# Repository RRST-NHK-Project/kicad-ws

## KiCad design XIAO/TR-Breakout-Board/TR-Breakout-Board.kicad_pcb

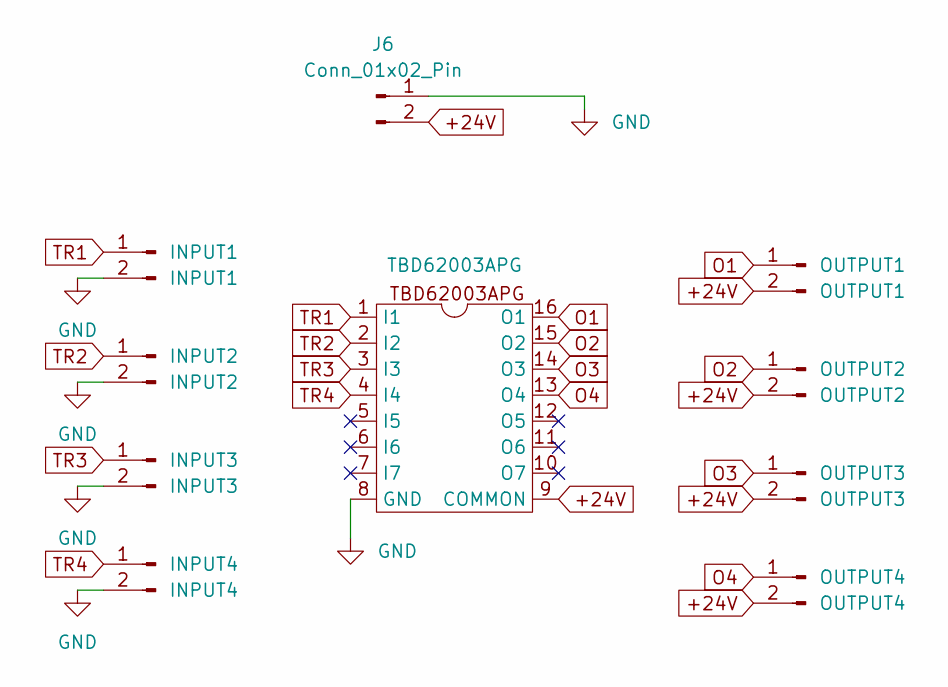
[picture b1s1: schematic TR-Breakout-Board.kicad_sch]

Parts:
INPUT1: INPUT1; JST_XH_B2B-XH-A_1x02_P2.50mm_Vertical
INPUT2: INPUT2; JST_XH_B2B-XH-A_1x02_P2.50mm_Vertical
INPUT3: INPUT3; JST_XH_B2B-XH-A_1x02_P2.50mm_Vertical
INPUT4: INPUT4; JST_XH_B2B-XH-A_1x02_P2.50mm_Vertical
J6: Conn_01x02_Pin; AMASS_XT30U-M_1x02_P5.0mm_Vertical
OUTPUT1: OUTPUT1; JST_XH_B2B-XH-A_1x02_P2.50mm_Vertical
OUTPUT2: OUTPUT2; JST_XH_B2B-XH-A_1x02_P2.50mm_Vertical
OUTPUT3: OUTPUT3; JST_XH_B2B-XH-A_1x02_P2.50mm_Vertical
OUTPUT4: OUTPUT4; JST_XH_B2B-XH-A_1x02_P2.50mm_Vertical
TBD62003APG: DIP-16_W7.62mm

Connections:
+24V: J6.2, OUTPUT1.2, OUTPUT2.2, OUTPUT3.2, OUTPUT4.2, TBD62003APG.9 (COMMON); also elsewhere on the board
GND: INPUT1.2, INPUT2.2, INPUT3.2, INPUT4.2, J6.1, TBD62003APG.8 (GND); also elsewhere on the board
O1: OUTPUT1.1, TBD62003APG.16 (O1); also elsewhere on the board
O2: OUTPUT2.1, TBD62003APG.15 (O2); also elsewhere on the board
O3: OUTPUT3.1, TBD62003APG.14 (O3); also elsewhere on the board
O4: OUTPUT4.1, TBD62003APG.13 (O4); also elsewhere on the board
TR1: INPUT1.1, TBD62003APG.1 (I1); also elsewhere on the board
TR2: INPUT2.1, TBD62003APG.2 (I2); also elsewhere on the board
TR3: INPUT3.1, TBD62003APG.3 (I3); also elsewhere on the board
TR4: INPUT4.1, TBD62003APG.4 (I4); also elsewhere on the board

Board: 2 copper layers, 10 parts (0 on the bottom side), 10 nets, no tracks yet.

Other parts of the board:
TBD62003APG1: DIP-16_W7.62mm

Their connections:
+24V: TBD62003APG1.9 (COMMON); also elsewhere on the board
GND: TBD62003APG1.8 (GND); also elsewhere on the board
O1: TBD62003APG1.16 (O1); also elsewhere on the board
O2: TBD62003APG1.15 (O2); also elsewhere on the board
O3: TBD62003APG1.14 (O3); also elsewhere on the board
O4: TBD62003APG1.13 (O4); also elsewhere on the board
TR1: TBD62003APG1.1 (I1); also elsewhere on the board
TR2: TBD62003APG1.2 (I2); also elsewhere on the board
TR3: TBD62003APG1.3 (I3); also elsewhere on the board
TR4: TBD62003APG1.4 (I4); also elsewhere on the board

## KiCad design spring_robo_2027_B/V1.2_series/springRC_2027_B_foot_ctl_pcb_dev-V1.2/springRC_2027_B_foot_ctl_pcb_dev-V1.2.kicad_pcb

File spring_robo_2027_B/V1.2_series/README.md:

# V1.2 系 設計案

V1.1（EOD）で配線が成立しなかったため、部品構成を変えた6案をプロジェクトとして複製したもの。
回路の中身以外（基板外形・層構成・ネットクラス・部品ライブラリ）は全案共通。

## 命名規則

| 位置 | 記号 | 意味 |
|---|---|---|
| 接頭 | なし | エンコーダのバッファを廃止 |
| 接頭 | `b` | バッファを 0Ω抵抗からソルダージャンパ（既定開放）に変更 |
| 接頭 | `fb` | バッファを強制有効（選択用の 0Ω抵抗を廃止） |
| 接尾 | `cmp` | QI 拡張ヘッダ J8 / J9 あり |
| 接尾 | なし | QI 拡張ヘッダ J8 / J9 なし |
| 例外 | `org` | V1.1 のまま（バッファ + 0Ω選択式 + QI） |

## 一覧

| 案 | バッファ | QI | 部品 | ネット | ERC | エラー |
|---|---|---|---|---|---|---|
| `V1.2org`  | 0Ω選択式 | あり | 71 | 63 | 29 | 0 |
| `V1.2bcmp` | ジャンパ式 | あり | 71 | 63 | 29 | 0 |
| `V1.2b`    | ジャンパ式 | なし | 74 | 63 | 29 | 0 |
| `V1.2fb`   | 強制有効 | なし | 62 | 63 | 29 | 0 |
| `V1.2cmp`  | なし | あり | 51 | 51 | 29 | 0 |
| `V1.2`     | なし | なし | 54 | 51 | 29 | 0 |

ERC の29件は全て警告。意図的なネットエイリアス28件と、J1 のキャッシュシンボル差異1件。

バッファなし案（`V1.2cmp` / `V1.2`）は `ENC*_BUF` ネットを `ENC*` に統合したためネット数が 51 に減る。
QI なし案は J8 / J9 の削除で単ピンになったネットに TP8〜TP12 を追加している。

## 開発ライン

**`V1.2`**（バッファなし・QIなし）で配線を進める。

## 共通仕様

- U6 = ESP32-S3-WROOM-1-**N16R8**
  - Octal SPI PSRAM が IO35 / IO36 / IO37 を占有するため、この3本は使用不可
  - QIあり案では J9 の 11 / 12 / 13 番ピンが死にピン
  - QIなし案では TP9 / TP10 / TP11 が死にピン
  - 周囲温度 -40〜65℃（PSRAM ECC 有効時は 85℃、容量 1/16 減）
- CAN 終端は R20（120Ω）+ J16（ジャンパ）の直列で CAN_H - CAN_L 間
- 各プロジェクトは `lib/` と `fp-lib-table` / `sym-lib-table` を自前で持つ自己完結構成

## 既知の課題

- 全案とも基板が回路図と未同期。Pcbnew の「回路図から基板を更新」が必要
- 基板は V1.1 の配線（475セグメント / 89ビア）をそのまま継承しているため配線はやり直し
- J1 に `lib_symbol_mismatch` 警告が残る

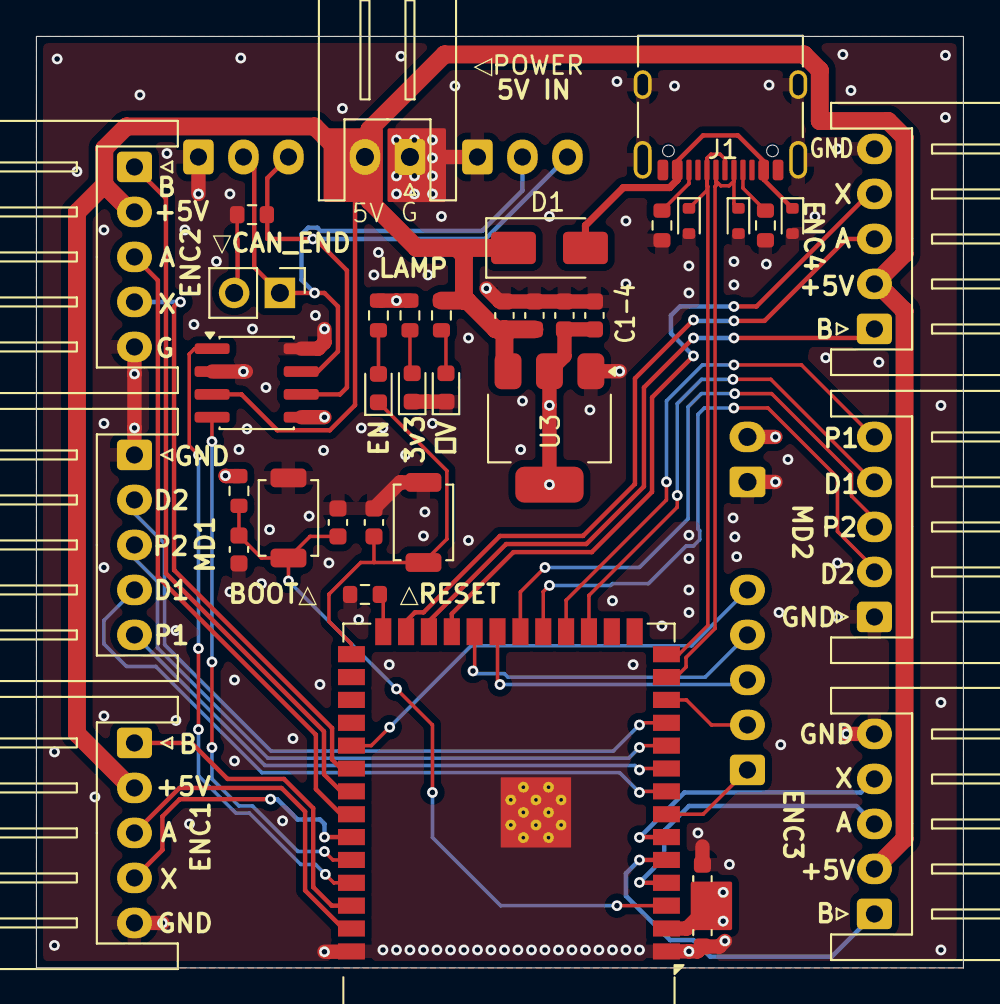
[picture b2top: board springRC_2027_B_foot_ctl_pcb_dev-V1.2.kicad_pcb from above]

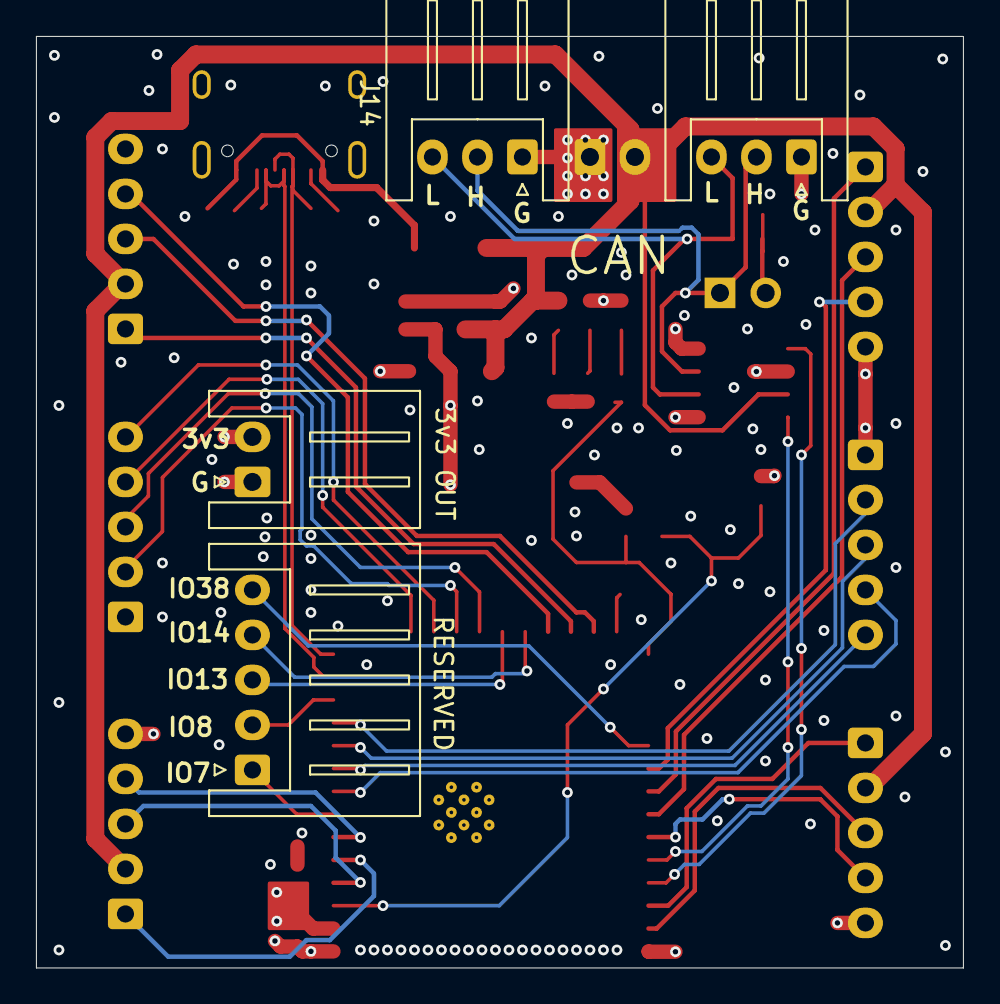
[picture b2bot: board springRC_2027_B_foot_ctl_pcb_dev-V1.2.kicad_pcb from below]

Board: 4 copper layers, 51.5 x 51.8 mm, 42 parts (4 on the bottom side), 44 nets.

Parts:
3v3 OUT: Conn_01x05_Socket; JST_XH_S5B-XH-A_1x05_P2.50mm_Horizontal
C1, C3, C7: 10uF; C_0603_1608Metric
C2, C4, C5, C6, C8: 100nF; C_0603_1608Metric
C9: 1uF; C_0603_1608Metric
D1: SS14; D_SMA
D2, D3, D4: LESD5D5.0CT1G; D_SOD-523
D5, D6, D7: LED; LED_0603_1608Metric
J1: USB_C_Receptacle_USB2.0_16P; USB_C_Receptacle_XKB_U262-16XN-4BVC11
J2, J3, J4, J5, J6, J7: Conn_01x05_Socket; JST_XH_S5B-XH-A_1x05_P2.50mm_Horizontal
J14, J15: Conn_01x03_Socket; JST_XH_S3B-XH-A_1x03_P2.50mm_Horizontal
J16: Conn_01x02_Pin; PinHeader_1x02_P2.54mm_Vertical
R1, R2, R3, R4: 5.1k; R_0603_1608Metric
R5: 10k; R_0603_1608Metric
R6: 330; R_0603_1608Metric
R19: 1k; R_0603_1608Metric
R20: 120; R_0603_1608Metric
RESERVED: Conn_01x02_Socket; JST_XH_S2B-XH-A_1x02_P2.50mm_Horizontal
SW1, SW2: SW_Push; SW_SPST_TS-1088-xR020
U1: MCP2562FD-E-SN; SOIC-8_3.9x4.9mm_P1.27mm
U3: LD1117S33TR_SOT223; SOT-223-3_TabPin2
U6: ESP32-S3-WROOM-1-N16R8; ESP32-S3-WROOM-1
◁POWER : Conn_01x02_Socket; JST_XH_S2B-XH-A_1x02_P2.50mm_Horizontal

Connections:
3V3: C3.2, C4.2, C7.1, C8.1, R2.1, R5.1, R6.2, RESERVED.2, U1.5 (Vio), U3.2 (VO), U6.2 (3V3)
+5V: C1.1, C2.1, D1.1 (K), J2.2, J3.2, J4.2, J5.2, R1.1, U1.3 (VDD), U3.3 (VI), ◁POWER.2
CAN_H: J14.2, J15.2, J16.1, U1.7 (CANH)
CAN_L: J14.3, J15.3, R20.1, U1.6 (CANL)
CAN_RX: U1.4 (RXD), U6.36 (RXD0)
CAN_TX: U1.1 (TXD), U6.37 (TXD0)
DN: D3.1, J1.A7 (D-), J1.B7 (D-), U6.13 (USB_D-)
DP: D4.1, J1.A6 (D+), J1.B6 (D+), U6.14 (USB_D+)
EN: C5.1, C9.1, R5.2, SW1.2, U6.3 (EN)
ENC1_A: J2.3, U6.39 (IO1)
ENC1_B: J2.1, U6.38 (IO2)
ENC1_X: J2.4, U6.35 (IO42)
ENC2_A: J3.3, U6.34 (IO41)
ENC2_B: J3.1, U6.33 (IO40)
ENC2_X: J3.4, U6.32 (IO39)
ENC3_A: J4.3, U6.25 (IO48)
ENC3_B: J4.1, U6.24 (IO47)
ENC3_X: J4.4, U6.23 (IO21)
ENC4_A: J5.3, U6.4 (IO4)
ENC4_B: J5.1, U6.5 (IO5)
ENC4_X: J5.4, U6.6 (IO6)
GND: C1.2, C2.2, C3.1, C4.1, C5.2, C6.2, C7.2, C8.2, C9.2, D2.2, D3.2, D4.2, D5.1 (K), D6.1 (K), J1.A1 (GND), J1.A12 (GND), J1.B1 (GND), J1.B12 (GND), J1.S1 (SHIELD), J2.5, J3.5, J4.5, J5.5, J6.1, J7.1, J14.1, J15.1, R3.2, R4.2, R19.2, RESERVED.1, SW1.1, SW2.1, U1.2 (VSS), U1.8 (STBY), U3.1 (GND), U6.1 (GND), U6.40 (GND), U6.41 (GND), ◁POWER.1
IO0: C6.1, D7.1 (K), SW2.2, U6.27 (IO0)
IO7: 3v3 OUT.1, U6.7 (IO7)
IO8: 3v3 OUT.2, U6.12 (IO8)
IO9: J7.4, U6.17 (IO9)
IO10: J7.5, U6.18 (IO10)
IO11: J7.2, U6.19 (IO11)
IO12: J7.3, U6.20 (IO12)
IO13: 3v3 OUT.3, U6.21 (IO13)
IO14: 3v3 OUT.4, U6.22 (IO14)
IO15: J6.4, U6.8 (IO15)
IO16: J6.5, U6.9 (IO16)
IO17: J6.3, U6.10 (IO17)
IO18: J6.2, U6.11 (IO18)
IO38: 3v3 OUT.5, U6.31 (IO38)
IO45: R19.1, U6.26 (IO45)
unnamed: D5.2 (A), R1.2
unnamed: D6.2 (A), R2.2
unnamed: D7.2 (A), R6.1
unnamed: J1.A5 (CC1), R4.1
unnamed: J1.B5 (CC2), R3.1
unnamed: J16.2, R20.2
VBUS: D1.2 (A), D2.1, J1.A4 (VBUS), J1.A9 (VBUS), J1.B4 (VBUS), J1.B9 (VBUS)

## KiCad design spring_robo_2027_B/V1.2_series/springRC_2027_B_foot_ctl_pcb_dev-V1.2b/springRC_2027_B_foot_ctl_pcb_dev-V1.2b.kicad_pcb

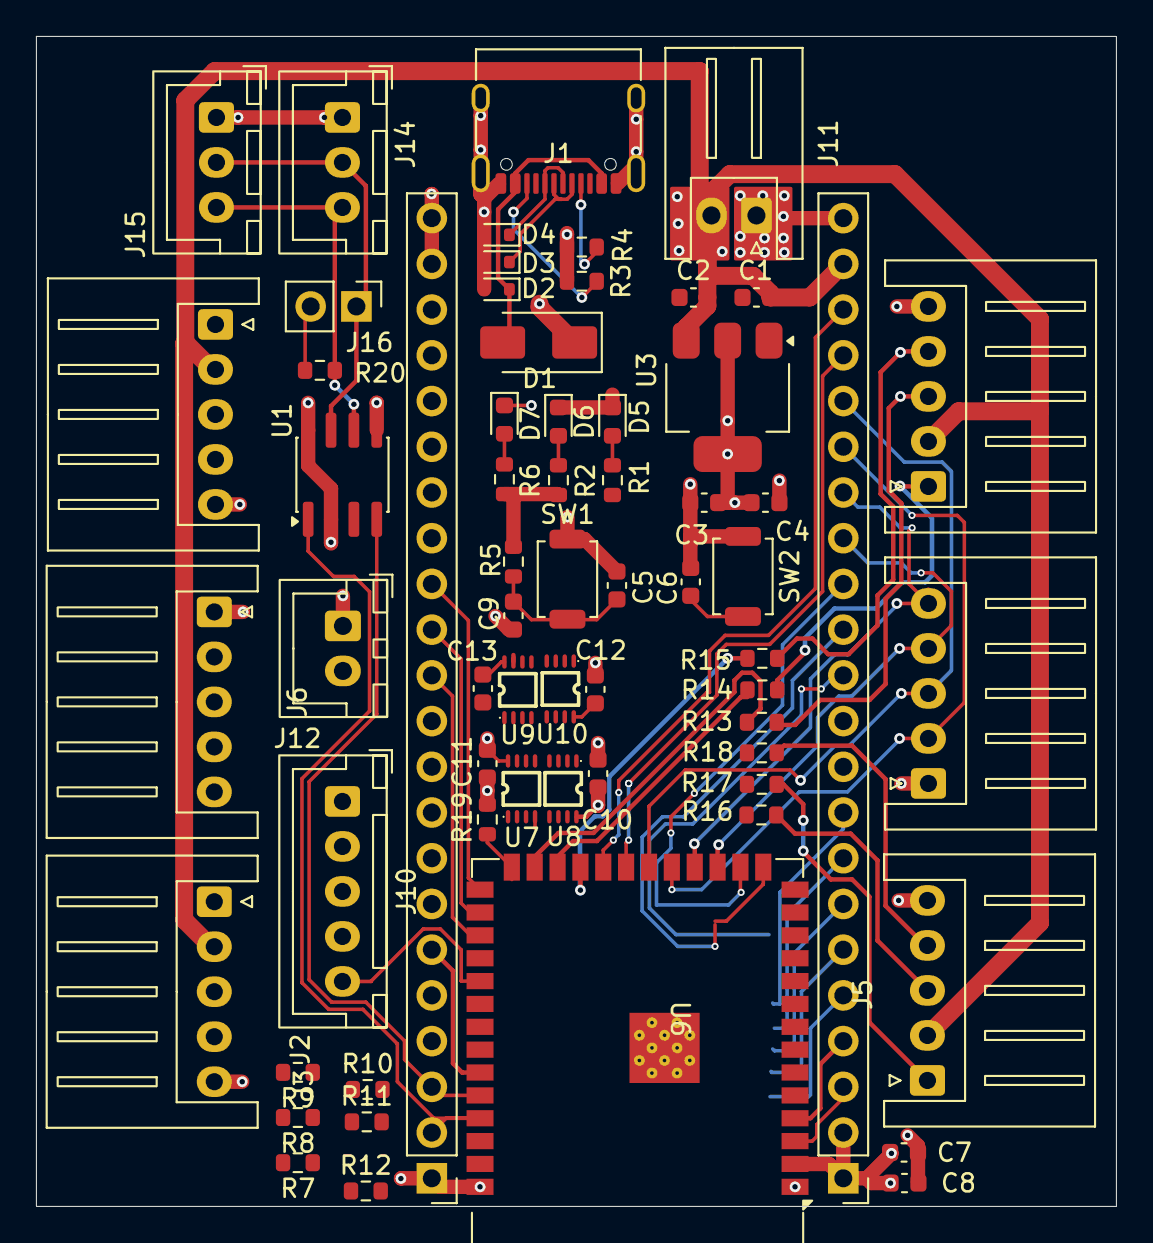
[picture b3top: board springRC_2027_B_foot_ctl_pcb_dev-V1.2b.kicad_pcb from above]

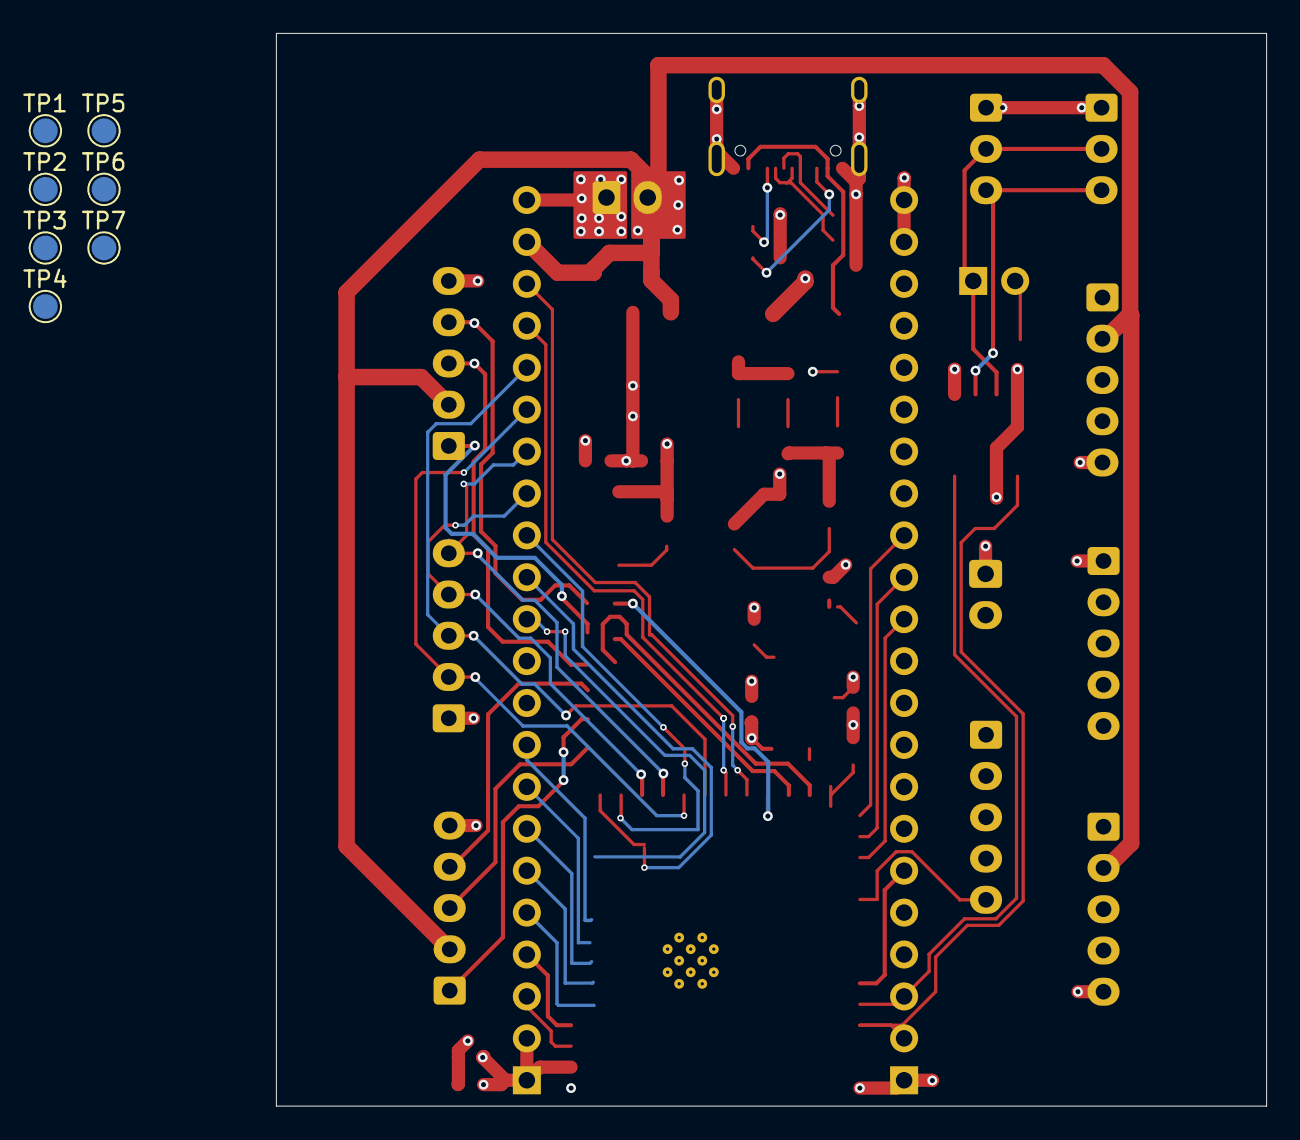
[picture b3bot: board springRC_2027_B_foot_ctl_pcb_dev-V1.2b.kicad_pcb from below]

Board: 4 copper layers, 60.0 x 65.0 mm, 71 parts (7 on the bottom side), 61 nets.

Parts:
C1, C3, C7: 10uF; C_0603_1608Metric
C2, C4, C5, C6, C8, C10, C11, C12, C13: 100nF; C_0603_1608Metric
C9: 1uF; C_0603_1608Metric
D1: SS14; D_SMA
D2, D3, D4: LESD5D5.0CT1G; D_SOD-523
D5, D6, D7: LED; LED_0603_1608Metric
J1: USB_C_Receptacle_USB2.0_16P; USB_C_Receptacle_XKB_U262-16XN-4BVC11
J2, J3, J4, J5, J6, J7: Conn_01x05_Socket; JST_XH_S5B-XH-A_1x05_P2.50mm_Horizontal
J8, J9: Conn_01x22_Pin; PinHeader_1x22_P2.54mm_Vertical
J10: Conn_01x05_Socket; JST_XH_B5B-XH-A_1x05_P2.50mm_Vertical
J11: Conn_01x02_Socket; JST_XH_S2B-XH-A_1x02_P2.50mm_Horizontal
J12: Conn_01x02_Socket; JST_XH_B2B-XH-A_1x02_P2.50mm_Vertical
J14, J15: Conn_01x03_Socket; JST_XH_B3B-XH-A_1x03_P2.50mm_Vertical
J16: Conn_01x02_Pin; PinHeader_1x02_P2.54mm_Vertical
R1, R2, R3, R4: 5.1k; R_0603_1608Metric
R5: 10k; R_0603_1608Metric
R6: 330; R_0603_1608Metric
R7, R8, R9, R10, R11, R12, R13, R14, R15, R16, R17, R18: 0R; R_0603_1608Metric
R19: 1k; R_0603_1608Metric
R20: 120; R_0603_1608Metric
SW1, SW2: SW_Push; SW_SPST_TS-1088-xR020
TP1: VBUS; TestPoint_Pad_D1.5mm
TP2: CAN_H; TestPoint_Pad_D1.5mm
TP3: CAN_L; TestPoint_Pad_D1.5mm
TP4, TP7: GND; TestPoint_Pad_D1.5mm
TP5: DP; TestPoint_Pad_D1.5mm
TP6: DN; TestPoint_Pad_D1.5mm
U1: MCP2562FD-E-SN; SOIC-8_3.9x4.9mm_P1.27mm
U3: LD1117S33TR_SOT223; SOT-223-3_TabPin2
U6: ESP32-S3-WROOM-1-N16R8; ESP32-S3-WROOM-1
U7, U8, U9, U10: SN74LVC3G17DCUR; VSSOP-8_L2.1-W2.4-P0.50-LS3.2-BR

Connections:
3V3: C3.2, C4.2, C7.1, C8.1, C10.1, C11.1, C12.1, C13.1, J8.1, J8.2, J12.2, R2.1, R5.1, R6.2, U1.5 (Vio), U3.2 (VO), U6.2 (3V3), U7.8 (VCC), U8.8 (VCC), U9.8 (VCC), U10.8 (VCC)
+5V: C1.1, C2.1, D1.1 (K), J2.2, J3.2, J4.2, J5.2, J8.21, J11.2, R1.1, U1.3 (VDD), U3.3 (VI)
CAN_H: J14.2, J15.2, J16.1, TP2.1 (1_1), U1.7 (CANH)
CAN_L: J14.3, J15.3, R20.1, TP3.1 (1_1), U1.6 (CANL)
CAN_RX: J9.3, U1.4 (RXD), U6.36 (RXD0)
CAN_TX: J9.2, U1.1 (TXD), U6.37 (TXD0)
DN: D3.1, J1.A7 (D-), J1.B7 (D-), J9.20, TP6.1 (1_1), U6.13 (USB_D-)
DP: D4.1, J1.A6 (D+), J1.B6 (D+), J9.19, TP5.1 (1_1), U6.14 (USB_D+)
EN: C5.1, C9.1, J8.3, R5.2, SW1.2, U6.3 (EN)
ENC1_A: J2.3, R7.1, U7.1 (1A)
ENC1_A_BUF: J9.4, R7.2, U6.39 (IO1), U7.7 (1Y)
ENC1_B: J2.1, R8.1, U7.3 (2A)
ENC1_B_BUF: J9.5, R8.2, U6.38 (IO2), U7.5 (2Y)
ENC1_X: J2.4, R9.1, U7.6 (3A)
ENC1_X_BUF: J9.6, R9.2, U6.35 (IO42), U7.2 (3Y)
ENC2_A: J3.3, R10.1, U8.1 (1A)
ENC2_A_BUF: J9.7, R10.2, U6.34 (IO41), U8.7 (1Y)
ENC2_B: J3.1, R11.1, U8.3 (2A)
ENC2_B_BUF: J9.8, R11.2, U6.33 (IO40), U8.5 (2Y)
ENC2_X: J3.4, R12.1, U8.6 (3A)
ENC2_X_BUF: J9.9, R12.2, U6.32 (IO39), U8.2 (3Y)
ENC3_A: J4.3, R13.1, U9.1 (1A)
ENC3_A_BUF: J9.16, R13.2, U6.25 (IO48), U9.7 (1Y)
ENC3_B: J4.1, R14.1, U9.3 (2A)
ENC3_B_BUF: J9.17, R14.2, U6.24 (IO47), U9.5 (2Y)
ENC3_X: J4.4, R15.1, U9.6 (3A)
ENC3_X_BUF: J9.18, R15.2, U6.23 (IO21), U9.2 (3Y)
ENC4_A: J5.3, R16.1, U10.1 (1A)
ENC4_A_BUF: J8.4, R16.2, U6.4 (IO4), U10.7 (1Y)
ENC4_B: J5.1, R17.1, U10.3 (2A)
ENC4_B_BUF: J8.5, R17.2, U6.5 (IO5), U10.5 (2Y)
ENC4_X: J5.4, R18.1, U10.6 (3A)
ENC4_X_BUF: J8.6, R18.2, U6.6 (IO6), U10.2 (3Y)
GND: C1.2, C2.2, C3.1, C4.1, C5.2, C6.2, C7.2, C8.2, C9.2, C10.2, C11.2, C12.2, C13.2, D2.2, D3.2, D4.2, D5.1 (K), D6.1 (K), J1.A1 (GND), J1.A12 (GND), J1.B1 (GND), J1.B12 (GND), J1.S1 (SHIELD), J2.5, J3.5, J4.5, J5.5, J6.1, J7.1, J8.22, J9.1, J9.21, J9.22, J11.1, J12.1, J14.1, J15.1, R3.2, R4.2, R19.2, SW1.1, SW2.1, TP4.1 (1_1), TP7.1 (1_1), U1.2 (VSS), U1.8 (STBY), U3.1 (GND), U6.1 (GND), U6.40 (GND), U6.41 (GND), U7.4 (GND), U8.4 (GND), U9.4 (GND), U10.4 (GND)
IO0: C6.1, D7.1 (K), J9.14, SW2.2, U6.27 (IO0)
IO3: J8.13, U6.15 (IO3)
IO7: J8.7, J10.1, U6.7 (IO7)
IO8: J8.12, J10.2, U6.12 (IO8)
IO9: J7.4, J8.15, U6.17 (IO9)
IO10: J7.5, J8.16, U6.18 (IO10)
IO11: J7.2, J8.17, U6.19 (IO11)
IO12: J7.3, J8.18, U6.20 (IO12)
IO13: J8.19, J10.3, U6.21 (IO13)
IO14: J8.20, J10.4, U6.22 (IO14)
IO15: J6.4, J8.8, U6.8 (IO15)
IO16: J6.5, J8.9, U6.9 (IO16)
IO17: J6.3, J8.10, U6.10 (IO17)
IO18: J6.2, J8.11, U6.11 (IO18)
IO35: J9.13, U6.28 (IO35)
IO36: J9.12, U6.29 (IO36)
IO37: J9.11, U6.30 (IO37)
IO38: J9.10, J10.5, U6.31 (IO38)
IO45: J9.15, R19.1, U6.26 (IO45)
IO46: J8.14, U6.16 (IO46)
unnamed: D5.2 (A), R1.2
unnamed: D6.2 (A), R2.2
unnamed: D7.2 (A), R6.1
unnamed: J1.A5 (CC1), R4.1
unnamed: J1.B5 (CC2), R3.1
unnamed: J16.2, R20.2
VBUS: D1.2 (A), D2.1, J1.A4 (VBUS), J1.A9 (VBUS), J1.B4 (VBUS), J1.B9 (VBUS), TP1.1 (1_1)

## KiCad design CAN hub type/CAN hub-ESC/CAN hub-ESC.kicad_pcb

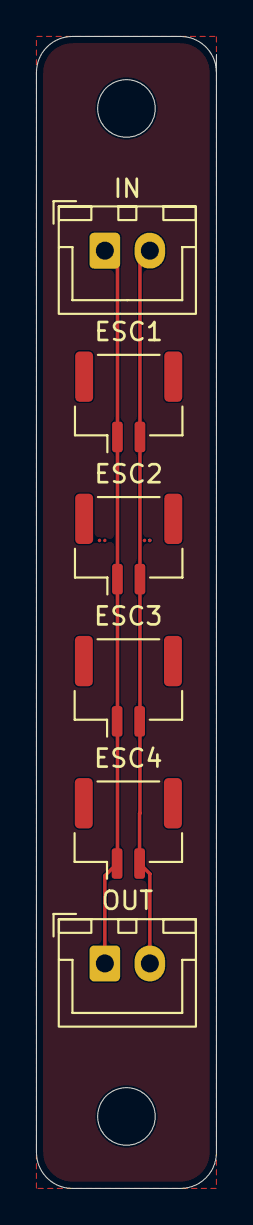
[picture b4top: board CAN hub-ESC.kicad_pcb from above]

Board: 2 copper layers, 10.0 x 64.0 mm, 6 parts (0 on the bottom side), 2 nets.

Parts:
ESC1, ESC2, ESC3, ESC4: CAN_BUS; JST_GH_BM02B-GHS-TBT_1x02-1MP_P1.25mm_Vertical
IN: CAN_BUS; JST_XH_B2B-XH-A_1x02_P2.50mm_Vertical
OUT: CAN_BUS; JST_XH_B2B-XH-A_1x02_P2.50mm_Vertical

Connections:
CANH: ESC1.1, ESC2.1, ESC3.1, ESC4.1, IN.1, OUT.1
CANL: ESC1.2, ESC2.2, ESC3.2, ESC4.2, IN.2, OUT.2

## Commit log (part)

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2025-07-29 esp用の基板追加
2025-07-29 フットプリント割り当て
2025-07-29 ３Dできた
2025-07-29 3d干渉OK
2025-07-29 自動配線前のやつ
2025-07-30 完成かも
2025-07-30 １００×１００
2025-07-30 モタドラ３つバージョンの自動配線前
2025-07-30 藤澤くん頑張りました～
2025-07-30 ようやく少し進みました！！！！！！！！！！！！！！！！！！！！！！！！！！！！！！！！！！！
2025-07-31 自動配線前
2025-07-31 自動配線後
2025-07-31 PCB作りました、疲れました、寝たいです
2025-08-01 テキスト入力、自動配線し直し、穴あけ
2025-08-02 ESP割り当て
2025-08-02 100になれなかったモタドラ4枚
2025-08-03 モタドラ４つT完成 田代先輩確認お願いします
2025-08-04 配線変更
2025-08-05 PCB再設計完了!!!!
2025-08-05 基盤購入しました!!!!
2025-08-07 作り直しv2でし
2025-08-07 kakunin
2025-08-08 ESP試作ボードの追加（自動配線前）
2025-08-10 配線済み
2025-08-10 シルクの追加と修正、お盆休み開始
2025-08-12 productionに入れてます
2025-08-13 ESP用アクチュエータ基板の追加
2025-08-22 finish
2025-09-10 V1.1追加
2025-09-11 配線できたよー
2025-09-11 MOUT1,2
2025-09-11 これで完成と言うことに勝手にしておきますねむい
2025-09-11 V1.1 CADデータの追加
2025-09-11 MDの製造ファイルを出力
2025-09-12 EST32カスタムボードの追加
2025-09-12 EST32カスタムボードの修正
2025-09-12 ESP32-ROS-IO-CE-V1.0
2025-09-12 RRST-ESP32 Rev.1
2025-10-02 回路図にわかりやすくテキスト入れただけでPCB側の変更はしてないです
2025-10-02 セラコンこの大きさでいいですか？
2025-10-02 今から頑張ります
2025-10-02 授業受けます！
2025-10-02 詰め詰め
2025-10-03 配線中,,,
2025-10-03 塗りつぶしゾーンを描きたい
2025-10-03 塗りつぶしたら未配線35でした泣
2025-10-03 塗りつぶしが何も機能していなかっただけでしたが、未配線20...
2025-10-03 あと13
2025-10-03 配線完了つかれたねたい
2025-10-03 サーマルリリーフのギャップを0.1mm、スポーク幅を1.2mmにしたよー
2025-10-03 あ配線途中からてきとうにやりすぎて回路に影響がないかしんぱいです シルク印刷と塗りつぶし配線終わってエラーゼロにして、警告は50個です あとやることなんですか？？？？？？？？？？？？？？？
2025-10-04 あ-三層になっちゃった
2025-10-04 あ-四層になっちゃった
2025-10-04 製造ファイル出力、発注！たぶん大丈夫、、、たぶん、知らんけど
2025-10-20 ピンの再割り当て完了
2025-10-23 パズルタイムが始まるよー、XT横向きになったよー
2025-10-23 詰めた、配線する
2025-10-23 やりなおし
2025-10-23 がんばるんば
2025-10-23 本当の配線前
2025-10-24 配線前確認よろしくお願いします！
2025-10-24 ちぇっくかんりょう
2025-10-26 ねようみんな
2025-10-27 塗りつぶしたので確認お願いします！！
2025-10-27 XT以外のところってパッド接続実線じゃなくていいですか？
2025-10-27 一旦停止
2025-10-27 配線おねがいします
2025-10-27 配線終わりましたけど
2025-10-27 これ塗りつぶしが配線避けてくれないからそれを考慮した配線をしなくてはならなくね？ということに終了直前に気がついたのですが気のせいです。
2025-10-27 もう配線しなおし！やり直し全部！おわり！おわり、
2025-10-27 不要な塗りつぶしを削除、二層にして横向きXTにするということは基盤を大きくしてもいいということだ。
2025-10-27 ようはこういうことですよね
2025-10-27 一旦詰み
2025-10-28 無理矢理完成
2025-10-28 いや無理じゃね？
2025-10-29 一応コピーとって、配置変え開始
2025-10-29 配置変え前
2025-10-29 配置変え後
2025-10-29 一旦保存
2025-10-30 めんどくさそうな詰みそうなところの配線前
2025-10-30 これは？
2025-10-30 MDv3完成、発注に取り掛かる
2025-10-30 名前を変えただけ
2025-11-06 名前変更、整理
2025-11-06 整理整頓
2025-11-06 XT60PW-Mどっかいってもたーください
2025-11-06 綺麗になったよ☺
2025-11-06 春ロボ基板追加
2025-11-06 MD追加
2025-11-06 PCB開始
2025-11-10 外付けシリアル用の回路を追加（ピン未割り当て）
2025-11-10 シリアル変換モジュールのデータシートを追加
2025-11-10 外部シリアルにピンを割り当て
2025-11-13 Gerberをzip形式に圧縮、発注したい
2025-11-13 割り当てした
2025-11-15 XT30UPB-Mのフットプリントが入らん
2025-11-17 たすけてたしろさん
2025-11-17 COMMENT
2025-11-18 また変更したよ
2025-11-18 回路図変更
2025-11-18 やり直しだけど、XTの立体像ついかしたからなんとなくわかりやすいと思う
2025-11-18 授業中続きやるよー
2025-11-19 お姉さん基板これを元に頑張ってください
2025-11-19 発注元が空気を読んで私のミスを修正してくれますように
2025-11-20 え四方にMD乗せるってことですか？たしろさん
2025-11-20 step追加
2025-11-20 Revert "step追加"
    This reverts commit 891872a3ed6071b190a0777538c0ca4b6c1cc20c.
2025-11-20 XT30のフットプリントを追加
2025-11-20 なんでXTの位置間合わないんだ、だるい
2025-11-20 (T_T)
2025-11-21 3Dモデルがないため、オスで無理矢理ぽくする
2025-11-22 配置し直し
2025-11-22 接触しないよう変更
2025-11-22 配線前2
2025-11-25 確認お願いします
2025-12-01 配置し直し確認お願いします
2025-12-01 眠いながら頑張りました。
2025-12-01 一旦配線前満足☺
2025-12-01 手配線した☺
2025-12-01 配線済☺
2025-12-01 メイン基板完成☺
2025-12-03 ベタGND追加後発注ok
2025-12-03 シルクの修正、あとはベタGNDだけ忘れずに
2025-12-04 メイン基板かんせーーー
2025-12-04 メイン基板発注します
2025-12-08 kansei
2025-12-12 v4回路図
2025-12-12 配置途中
2025-12-12 配線のために配置変え
2025-12-12 一旦表面実装の部品探しの旅に出ます
2026-01-10 メイン基板変更進捗
2026-01-28 修正配線済みのメイン基板
2026-01-29 配線する
2026-01-29 自動配線
2026-01-29 自動配線何回目なんや
2026-01-29 自動配線そろそろさせてくれ
2026-01-30 配線途中
2026-01-31 手配線前
2026-02-05 割り当てしたい
2026-02-06 回路図変更3
2026-02-06 回路図変更4
2026-02-12 回路図確定
2026-02-12 フットプリント割り当てし直し
2026-02-12 atohaisenikko
2026-02-12 dekitayo
2026-02-12 yarinaoshi
2026-02-12 kansei?
2026-02-12 発注する
2026-02-12 回路図変更により自動配線し直し
2026-02-12 かんせー
2026-02-12 お わ り
2026-02-19 シルク入れる前
2026-02-19 製造ファイル出力
2026-02-19 シルクやり直し
2026-02-19 シルクやり直し２
2026-02-19 製造ファイル出力2
2026-02-19 製造ファイル出力3
2026-03-04 自動配線まで
2026-03-11 新MD用のESP32-S3の基板回路図
2026-03-11 旧MD用のESP32-S3の基板回路図
2026-03-11 てきとうはいち
2026-03-11 アクチュエーター数変更
2026-03-11 一応ちゃんと配置
2026-03-11 新MD配置
2026-03-11 旧MD配置決めシルク完了１
2026-03-11 旧MD配置決めシルク完了２
2026-03-13 藤井よろぴく
2026-03-15 XT30メスのフットプリントがほしい
2026-03-16 配置決め
2026-03-16 モタドラ動確取ってから考える
2026-03-18 CAN hub 2
2026-03-18 CAN hub 3
2026-03-18 CAN hub 5
2026-03-18 CAN hub
2026-03-18 製造出力
2026-03-18 表面実装にしたいがすべて互換があるわけではない
2026-03-19 フォルダ整理
2026-03-19 PHのフットプリントをどれか当てよう
2026-03-20 XIAO ESP32s3
2026-03-20 変換基板、XIAOの回路図途中
2026-03-20 回路図ほぼ確定？
2026-03-20 変換基板一応できた
2026-03-21 基板ほぼ完成
2026-03-21 変換基板ほぼかんせ
2026-03-21 基板ほぼかんせ ねむい
2026-03-22 とりあえず基板二つ完成しましたよ、あとメイン基板届いた
2026-03-22 ビア忘れてた
2026-03-24 ええんちゃうの
2026-03-24 発注すんで
2026-04-02 step出力
2026-04-30 ESPノーマルのstep
2026-05-07 output専用
2026-05-07 専用基板作るんやから良い設計が上がることを期待しています
2026-05-09 足回り専用基板
2026-05-09 can回路確認中、確認次第配線ベタグラウンド
2026-05-09 ESP32-ROS-IO-susp-V1.0
2026-05-14 ESP32-S3-Sense
2026-05-14 can回路待ち
2026-05-14 自動配線&未配線の手直し完了
2026-05-15 マイコンにセンサ入力を増設
2026-05-15 シルク修正まだ
2026-05-17 スクラップ＆ビルド
2026-05-18 仮配置完了、拡張基板設計開始
2026-05-18 拡張基板、外形線
2026-05-18 拡張基盤迷走中
2026-05-21 回路図できた
2026-05-21 PCB大体完成
2026-05-21 10かけ10に収まらない
2026-05-21 10×10に収まらないだけでそれ以外はできた
2026-05-23 どうにかする
2026-05-28 自動配線前2
2026-05-28 自動配線前3
2026-05-28 自動配線前4
2026-05-28 自動配線前desu
2026-05-28 基板完成
2026-05-29 あろはあってます。これ最新版
2026-06-04 IRLB3813
2026-06-04 IRLB3813,L7805CV,L7812CV,74HC08N,78HC14NをSMDにして回路図完成
2026-06-05 色々やってみよう
2026-06-05 とりあえず配置
2026-06-05 ちょっと変えた
2026-06-10 BLDCMD作成中...
2026-06-11 XIAO-S3の表面実装途中
2026-06-11 XIAO-S3の表面実装配置前
2026-06-11 ライブラリ用ディレクトリの作成
2026-06-11 XIAO S3の配置、配線前
2026-06-11 電源ライン配線前
2026-06-11 電源ラインの配線
2026-06-11 一晩寝かせよう
2026-06-17 製造データ出力
2026-06-18 aloha動確した？
2026-06-25 回路図２
2026-06-25 やり直し
2026-06-25 これならいけるか
2026-06-28 一旦前までのBLDCMDver.1.1提出
